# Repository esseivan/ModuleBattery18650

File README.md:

# 18650 Battery module

## Schematic

[Link](./fabrication/pdf/ModuleBattery18650.pdf)

## 3D
The footprint of the mosfets have been changed. The PCB is not finished yet

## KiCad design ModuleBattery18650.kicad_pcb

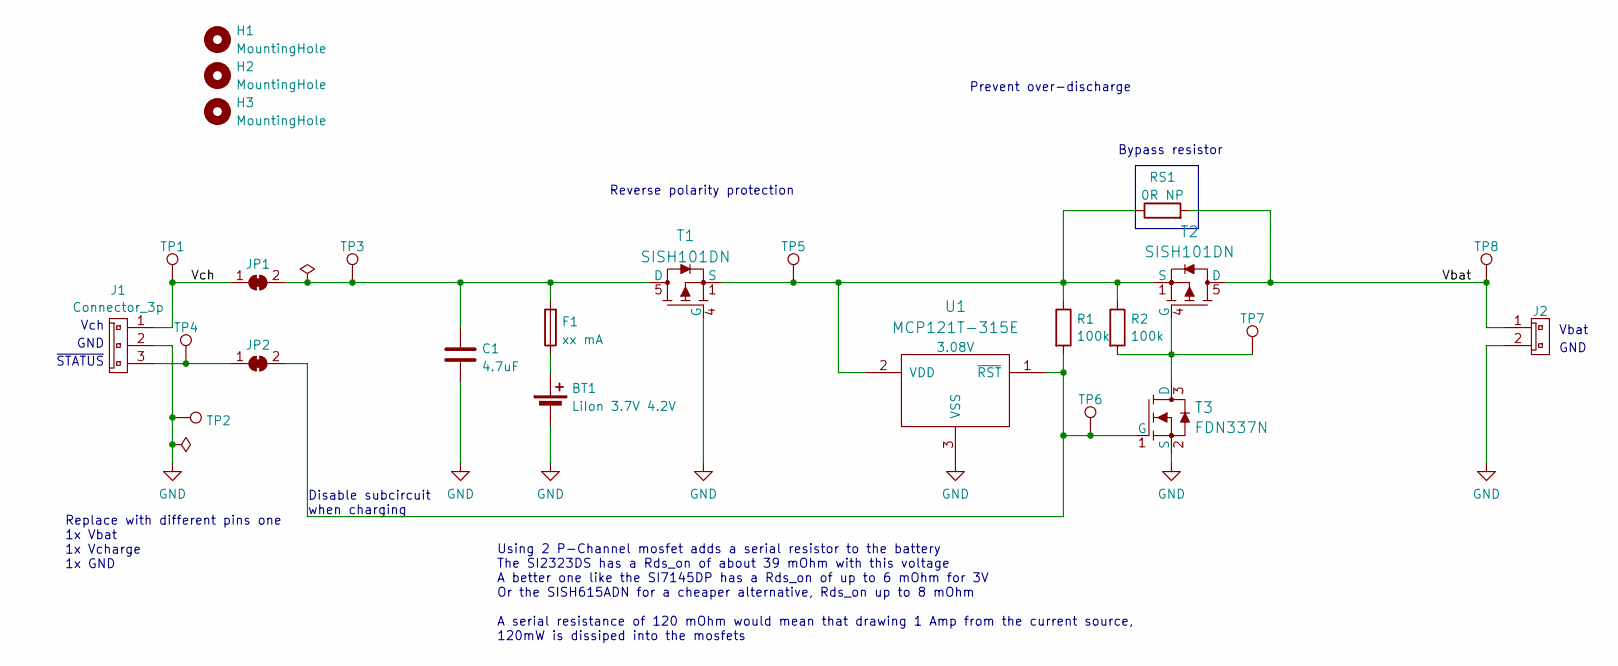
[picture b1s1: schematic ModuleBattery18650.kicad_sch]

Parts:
BT1: LiIon 3.7V 4.2V; 18650_Battery_holder
C1: 4.7uF; C_0805_2012Metric_Pad1.18x1.45mm_HandSolder
F1: xx mA; Fuse_1206_3216Metric_Pad1.42x1.75mm_HandSolder
H1, H2, H3: MountingHole; MountingHole_4.3mm_M4
J1: Connector_3p; Connector_3p_m
J2: Connector_2p_r; Connector_2p_m
JP1, JP2: SolderJumper_2_Bridged; SolderJumper-2_P1.3mm_Open_RoundedPad1.0x1.5mm
R1, R2: 100k; R_0603_1608Metric_Pad0.98x0.95mm_HandSolder
RS1: 0R NP; R_0603_1608Metric_Pad0.98x0.95mm_HandSolder
T1, T2: SISH101DN; PowerPAK 1212-8S
T3: FDN337N; SOT-23_Handsoldering
TP1, TP2, TP3, TP4, TP5, TP6, TP7, TP8: TestPoint; TestPoint_Pad_D1.0mm
U1: MCP121T-315E; SOT-23_Handsoldering; Voltage 3.08V

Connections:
/Vbat: J2.1, RS1.2, T2.5 (D), TP8.1
/Vch: J1.1, JP1.1 (A), TP1.1
GND: BT1.2 (-), C1.2, J1.2, J2.2, T1.4 (G), T3.2 (S), TP2.1, U1.3 (VSS)
unnamed: BT1.1 (+), F1.1
unnamed: J1.3, JP2.1 (A), TP4.1
unnamed: C1.1, F1.2, JP1.2 (B), T1.5 (D), TP3.1
unnamed: JP2.2 (B), R1.2, T3.1 (G), TP6.1, U1.1 (~RST)
unnamed: R2.2, T2.4 (G), T3.3 (D), TP7.1
unnamed: R1.1, R2.1, RS1.1, T1.1 (S), T1.2 (S), T1.3 (S), T2.1 (S), T2.2 (S), T2.3 (S), TP5.1, U1.2 (VDD)

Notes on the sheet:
~{STATUS}
Reverse polarity protection
Replace with different pins one 1x Vbat 1x Vcharge 1x GND
Bypass resistor
Vch
Using 2 P-Channel mosfet adds a serial resistor to the battery The SI2323DS has a Rds_on of about 39 mOhm with this voltage A better one like the SI7145DP has a Rds_on of up to 6 mOhm for 3V Or the SISH615ADN for a cheaper alternative, Rds_on up to 8 mOhm A serial resistance of 120 mOhm would mean 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
GND
Prevent over-discharge
Vbat
Disable subcircuit when charging

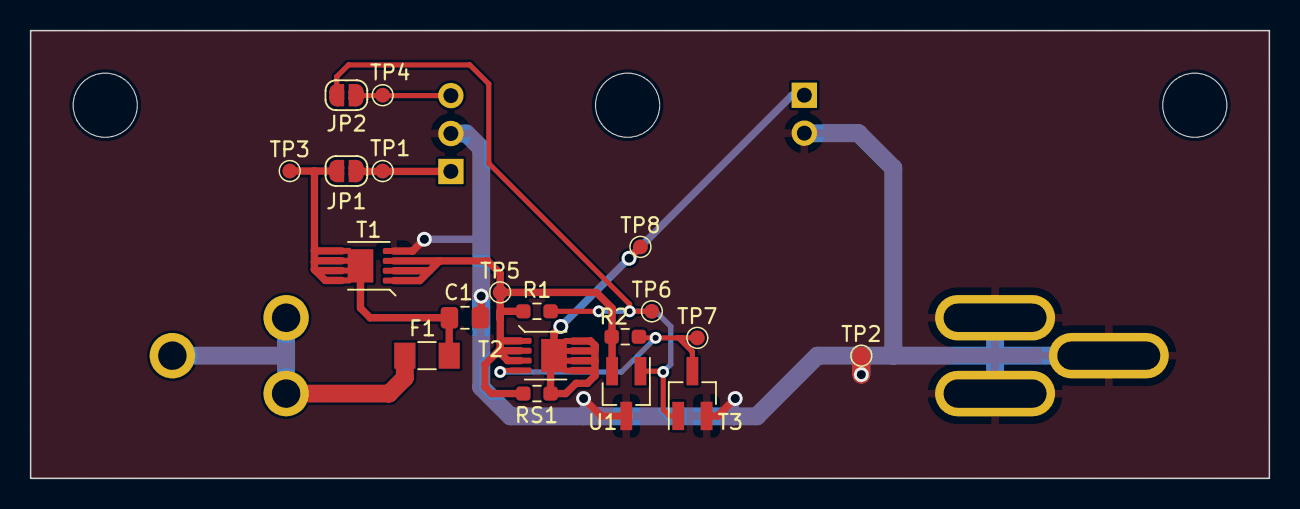
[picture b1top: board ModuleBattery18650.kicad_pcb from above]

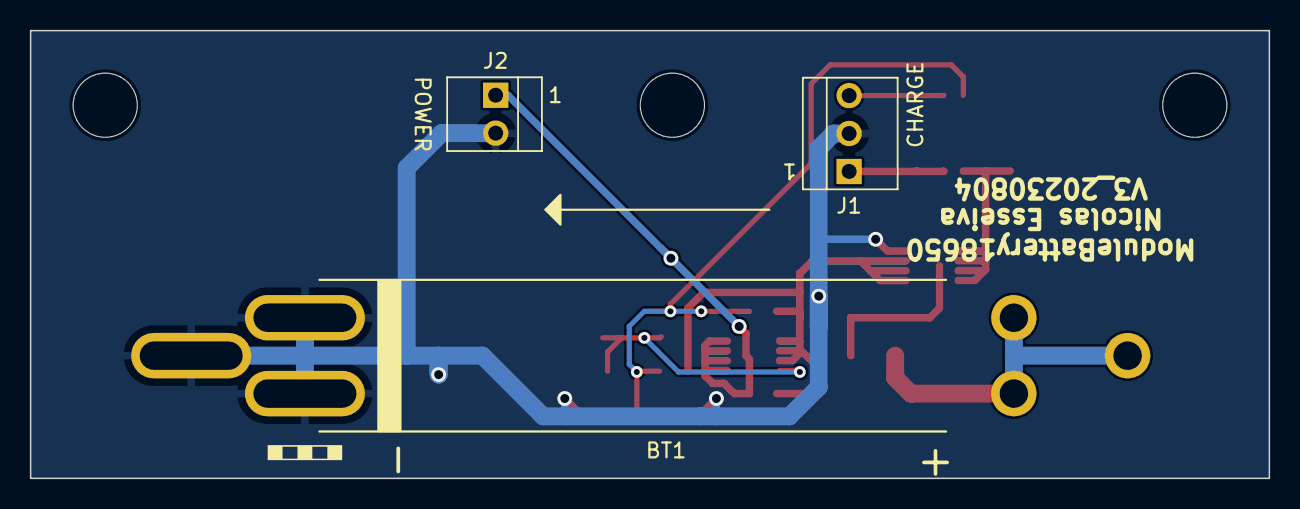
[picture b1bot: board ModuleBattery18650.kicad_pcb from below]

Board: 2 copper layers, 83.0 x 30.0 mm, 25 parts (3 on the bottom side), 9 nets.

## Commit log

2022-09-11 corrected mosfet model
2022-09-11 Changed mosfets models to SISH615ADN
2022-09-11 adapted footprints
2022-09-17 added output files
2022-09-17 edit readme schematic
2022-09-22 progress for the pcb
2022-09-24 progress on pcb
2023-04-02 pdfs
2023-04-08 rev00
2023-05-18 revision 01
2023-06-21 ^small changes
2023-07-03 r1 fabrication output
2023-07-04 porte batterie adapté
2023-07-05 Fixed portebatterie length
2023-08-04 modification schema
2023-08-04 Version 3
    Fixed schematic. Combined charge subcircuit disable and low voltage circuit cutoff
    charge connector now 3pin
    removed charge input reverse polarity protection
2025-07-03 misc: updated to KiCad 9 + added workflow
2025-07-03 fix: moved workflow file
2025-07-03 docs: added schematic, cleaned files
2025-07-03 misc: updated readme schematic
2025-07-03 misc: workflow test fix
2025-07-03 misc: removed cad files
